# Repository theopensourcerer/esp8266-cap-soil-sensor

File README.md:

# ESP8266 Capacitive Soil Moisture Sensor

## Table of Contents
* [Summary](#summary)
* [Hardware](#hardware)
* [Case](#case)
* [Code](#code)
* [Licenses](#licenses)

## Summary
This is a personal project to build a Capacitive Soil Moisture Sensor for my hobby of growing chillies.

The project consists of three parts: the hardware (PCB and Sensor(s) etc.(, the case to hold the sensor, and the software.

I wanted to design and build my own sensors with built in WiFi so they could operate "standalone" in my tunnel. I wanted them to run from a decent capacity battery such as an 18650 Li-ion and to be able to report back information at timely intervals to my home server and database. Ultimately I want to use this information to be able to automate the watering of my plants.

The Internet is a wonderful thing. I have spent many dark and long evenings through the 2016/17 winter, learning, reading and searching for information on Capacitive moisture sensors. There are numerous resources (and individual people behind each of them) I would like to thank for taking the time to design, document and discuss the various mechanisms for capacitive moisture measurement. Hopefully my own small contributions may help others in the future.

Why use capacitive sensors? 

* The cheap and traditional moisture sensor uses a resistive technique. That is, to put it simply, the probe usually consists of two electrically conductive "prongs" which are inserted into the soil with a known gap between them. As the moisture increases, the electrical resistance decreases. This technique works but is not ideal mostly due to electrolysis [1]. Essentially the probes deteriorate rapidly due to this phenomenom and hence the measurements also change and the probes need to be replaced quite frequently

* The resitive appraoch requires significantly more power (electric current) to operate than the capacitive technique, so battery life would be constrained

* The fundamental principle of the capacitive sensor is that you measure the time it takes for your capacitor (the probe) to charge. This charging period changes proportionately to the moisture level of the soil. It means there is no direct electrical contact between the soil and the probe (it is insulated) therefore should last a great deal longer

* It is harder to do; hence far more interesting to design and produce ;-)

Below is my list, in no particular order, of the online resources I found to be most helpful during my research (there were and are others; Google is your friend):

http://pcb.daince.net/doku.php?id=sensor_soil_2
http://zerocharactersleft.blogspot.co.uk/2011/11/pcb-as-capacitive-soil-moisture-sensor.html

https://www.dfrobot.com/wiki/index.php/Capacitive_Soil_Moisture_Sensor_SKU:SEN0193 (Bought one of these to test. It works)
https://github.com/Miceuz/i2c-moisture-sensor
and
https://wemakethings.net/chirp/ (Bought one of these - this works too)

http://www.instructables.com/id/Comparison-of-Capacitive-Soil-Probes/
and then
https://github.com/acolomitchi/cap-soil-moisture-v2 (I have used this probe design. Thanks acolomitchi)

Then I came across these few resources (thank you Google Translate)
* https://www.mikrocontroller.net/topic/335407

Which led me here:
* http://shop.thomasheldt.de/product_info.php?info=p90_giess-o-mat-sensor-kit.html (Bought a couple of these and they work)

Which then led me to:
* https://github.com/Zentris/erdfeuchtemessung

and
* https://github.com/lh84/moisture_sensor_esp12

I have also been following along with this project:
* https://luckyresistor.me/2017/02/08/how-to-design-a-cheap-plant-watering-sensor-part-1/
I really like the way this project has been analysed, designed and documented - much more so than mine which is a "try-something-and-see-if-it-works" approach.

These resources above gave me confidence that a custom design was possible so I set to work basing the Schematic and PCB on the work of the people above. The use of a Schmitt Trigger Inverter to "square" up the oscillations of the sensor probe means it can be read by pretty much any GPIO as long as the MCU is fast enough. The ESP8266 has some limitations in this regard so I considered using a half-wave rectifier to convert this to a simple analogue voltage but the work of Zentris and Lars(lh84) convinced me that the ESP8266 was capable of reading the frequency directly if it can be kept below about 150Khz.

This is _all_ still very much a work in progress. I have built a prototype board and have had it running on my desk but the results leave me rather confused :-(

## Hardware
The Schematic and PCB are designed in KiCAD. A version of this board has been fabricated but it is not the final version. Probably the most interesting part is the layout of the probe footprint itself. This came from acolomitchi as mentioned above. (I have modified the layout somewhat so it is more suited to an integrated PCB - I also made it a little longer as my target was for quite large pots).

## Case
The case is designed in OpenSCAD and is suitable for printing on a 3D Printer. The basic idea is that the PCB slides into the case. The PCB has about 1.5mm of empty space down each side of the board which should be enough to slot in place. The probe end of the PCB fits through the slot in the bottom of the case. There should be enough height to support the power connector (not tested) and the other half of the case holds an 18650 battery in a plastic holder. The "lid" screws on and has protrusions which should prevent the probe PCB and the battery from moving about too much. I plan to use something like silicon bathrooom sealant around the probe slot to prevent any moisture ingressing into the case. Please feel free to use and improve - within the terms of the license of course.

## Code
The software for the ESP8266 is in this directory. It should be fairly simple C code. The config.h file contains user-defined parameters. The ESP8266 code works like this: On power up the ESP attempts to connect to the WiFi network. If successful it then attempts to read the frequency of the capacitive sensor probe. If the Sensor probe is read successfully the data is formatted as a JSON object and sent to the MQTT broker. The ESP8266 also sends information about its supply voltage and the time it took to run this code loop. Finally the code puts the ESP into "Deep Sleep" for a preconfigured period.

## Licenses
* The software is GPL (http://www.gnu.org/licenses/) 
* The OpenSCAD case design, and the Schematic and PCB are Creative Commons Attribution-NonCommercial-ShareAlike 4.0 International Public License (https://creativecommons.org/licenses/by-nc-sa/4.0/)

[1] https://en.wikipedia.org/wiki/Electrolysis

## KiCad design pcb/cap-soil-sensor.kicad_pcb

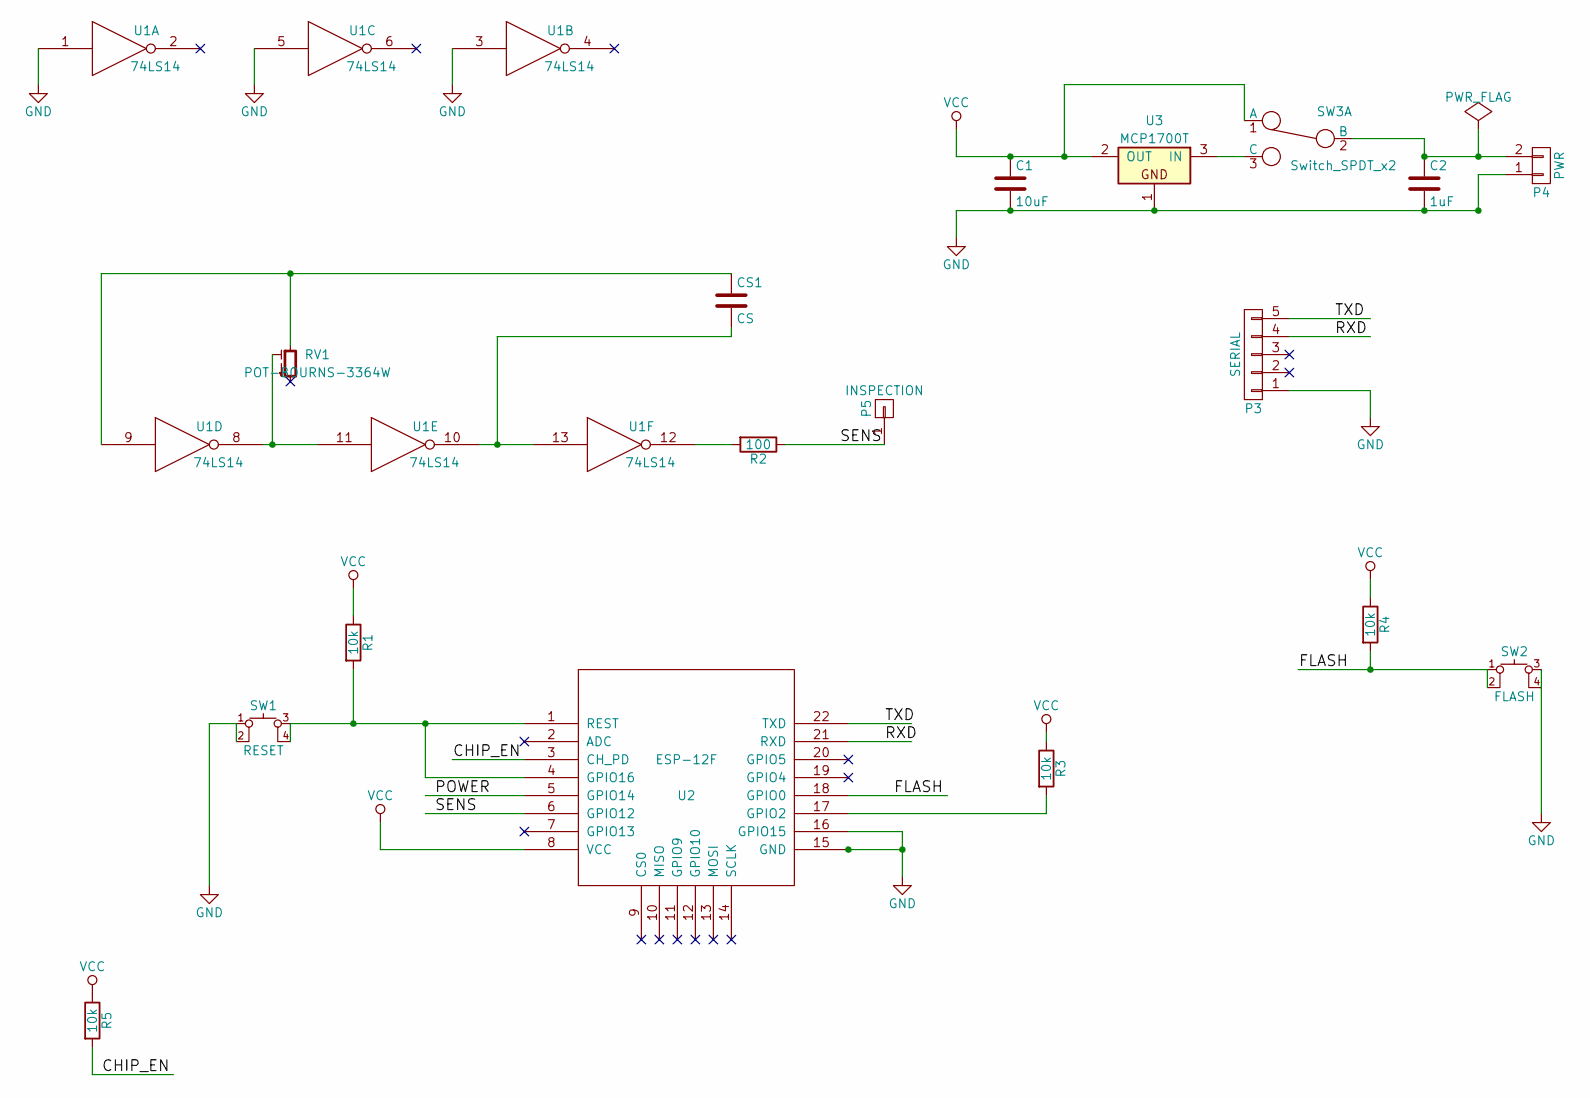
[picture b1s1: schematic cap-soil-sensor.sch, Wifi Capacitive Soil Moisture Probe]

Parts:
C1: 10uF; C_1206_HandSoldering
C2: 1uF; C_1206_HandSoldering
CS1: CS; cap_sensor_probe
P3: SERIAL; Pin_Header_Straight_1x05_Pitch2.54mm
P4: PWR; JST_XH_B02B-XH-A_02x2.50mm_Straight
P5: INSPECTION; Pin_Header_Straight_1x01_Pitch2.54mm
R1, R3, R4, R5: 10k; R_1206_HandSoldering
R2: 100; R_1206_HandSoldering
RV1: POT-BOURNS-3364W; BOURNS-3364-W
SW1: RESET; SKQGAFE010_Switch
SW2: FLASH; SKQGAFE010_Switch
SW3: Switch_SPDT_x2; SW_SPDT_PCM12
U1: 74LS14; SOIC-14_3.9x8.7mm_Pitch1.27mm
U2: ESP-12F; ESP-12E
U3: MCP1700T; SOT-23_Handsoldering

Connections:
/CHIP_EN: R5.2, U2.3 (CH_PD)
/FLASH: R4.2, SW2.1, SW2.2, U2.18 (GPIO0)
/RXD: P3.4, U2.21 (RXD)
/SENS: P5.1, R2.1, U2.6 (GPIO12)
/TXD: P3.5, U2.22 (TXD)
GND: C1.2, C2.2, P3.1, P4.1, SW1.1, SW1.2, SW2.3, U1.1, U1.3, U1.5, U1.7 (GND), U2.15 (GND), U2.16 (GPIO15), U3.1
unnamed: C2.1, P4.2, SW3.2 (B)
unnamed: CS1.1, RV1.3, U1.9
unnamed: CS1.2, U1.10, U1.13
unnamed: R1.2, SW1.3, SW1.4, U2.1 (REST), U2.4 (GPIO16)
unnamed: R2.2, U1.12
unnamed: R3.2, U2.17 (GPIO2)
unnamed: RV1.2, U1.8, U1.11
unnamed: SW3.3 (C), U3.3 (IN)
POWER: U1.14 (POWER), U2.5 (GPIO14)
VCC: C1.1, R1.1, R3.1, R4.1, R5.1, SW3.1 (A), U2.8 (VCC), U3.2 (OUT)

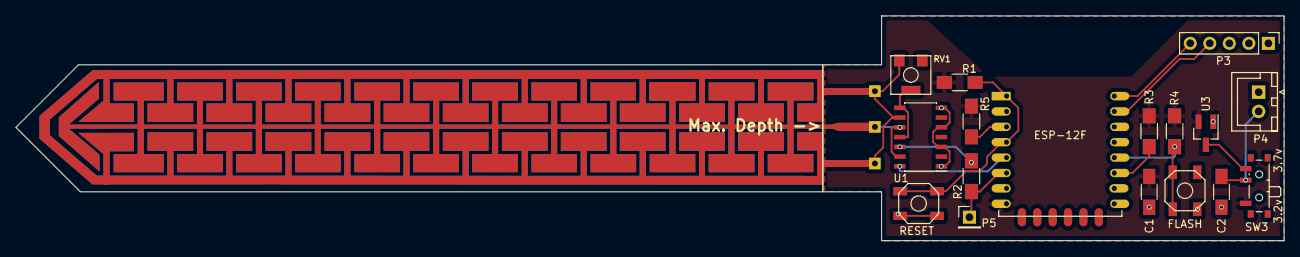
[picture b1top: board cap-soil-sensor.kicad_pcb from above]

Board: 2 copper layers, 164.8 x 29.2 mm, 18 parts (0 on the bottom side), 16 nets.

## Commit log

2017-04-24 Clean up and update static files
2020-06-27 Fix typo. Refs #1
2022-02-03 Update README.md
    Add image of PCB
